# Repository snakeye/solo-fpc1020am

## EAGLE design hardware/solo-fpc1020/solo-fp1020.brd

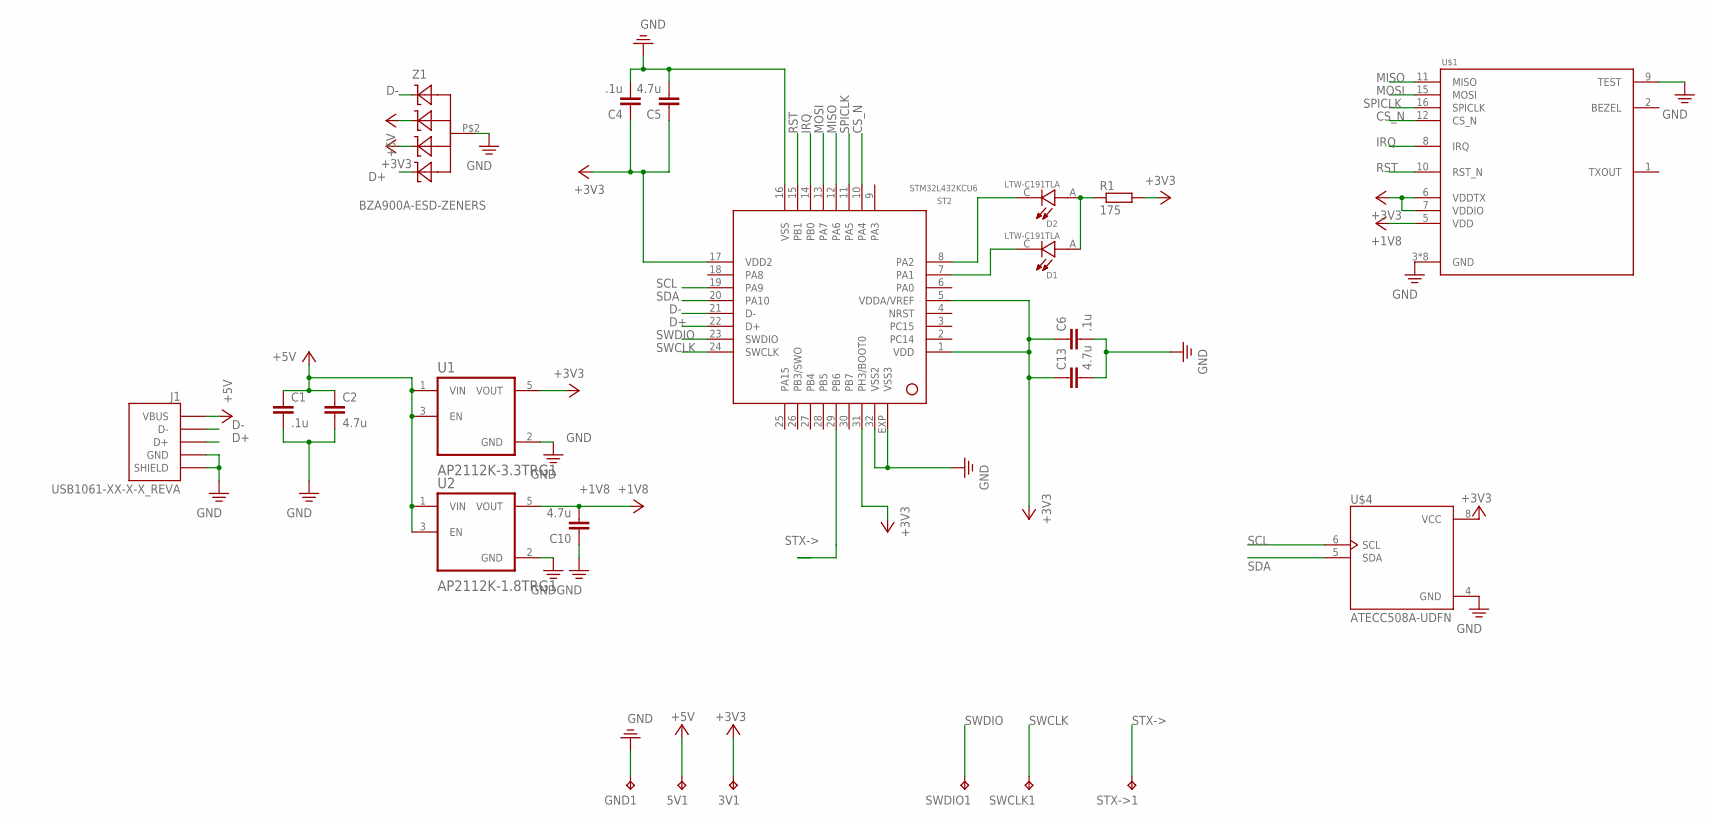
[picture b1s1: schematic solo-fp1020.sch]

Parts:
3V1, 5V1: TEST_POINT; B1,27
C1, C4, C6: .1u; C0603
C2, C5, C10, C13: 4.7u; C0603
D1, D2: LTW-C191TLA; LEDC1608X65N
GND1: TEST_POINT; B1,27
J1: USB1061-XX-X-X_REVA; GCT_USB1061-XX-X-X_REVA
R1: 175; R0603
ST2: STM32L432KCU6; QFN32
STX->1: TEST_POINT; B1,27
SWCLK1: TEST_POINT; B1,27
SWDIO1: TEST_POINT; B1,27
U1: AP2112K-3.3TRG1; SOT95P285X140-5N
U2: AP2112K-1.8TRG1; SOT95P285X140-5N
U$1: FPC1020AM
U$4: ATECC508A-UDFN; SON50P200X300X60-9N
Z1: BZA900A-ESD-ZENERS; BZA900A

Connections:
+1V8: C10.2, U2.5 (VOUT), U$1.5 (VDD)
+3V3: 3V1.TP, C4.1, C5.1, C6.1, C13.1, R1.2, ST2.1 (VDD), ST2.5 (VDDA/VREF), ST2.17 (VDD2), ST2.31 (PH3/BOOT0), U1.5 (VOUT), U$1.6 (VDDTX), U$1.7 (VDDIO), U$4.8 (VCC), Z1.P$5 (C1)
+5V: 5V1.TP, C1.1, C2.1, J1.1 (VBUS), U1.1 (VIN), U1.3 (EN), U2.1 (VIN), U2.3 (EN), Z1.P$1 (C)
CS_N: ST2.10 (PA4), U$1.12 (CS_N)
D+: J1.3 (D+), ST2.22 (D+), Z1.P$3 (C3)
D-: J1.2 (D-), ST2.21 (D-), Z1.P$4 (C2)
GND: C1.2, C2.2, C4.2, C5.2, C6.2, C10.1, C13.2, GND1.TP, J1.4 (GND), J1.5 (SHIELD), J1.6 (SHIELD), ST2.16 (VSS), ST2.32 (VSS2), ST2.EXP (VSS3), U1.2 (GND), U2.2 (GND), U$1.3 (GND), U$1.4 (GND), U$1.9 (TEST), U$1.13 (GND), U$1.14 (GND), U$1.17 (GND), U$1.18 (GND), U$1.19 (GND), U$1.20 (GND), U$4.4 (GND), Z1.P$2
IRQ: ST2.14 (PB0), U$1.8 (IRQ)
MISO: ST2.12 (PA6), U$1.11 (MISO)
MOSI: ST2.13 (PA7), U$1.15 (MOSI)
unnamed: D1.A, D2.A, R1.1
unnamed: D2.C, ST2.8 (PA2)
unnamed: D1.C, ST2.7 (PA1)
RST: ST2.15 (PB1), U$1.10 (RST_N)
SCL: ST2.19 (PA9), U$4.6 (SCL)
SDA: ST2.20 (PA10), U$4.5 (SDA)
SPICLK: ST2.11 (PA5), U$1.16 (SPICLK)
STX->: ST2.29 (PB6), STX->1.TP
SWCLK: ST2.24 (SWCLK), SWCLK1.TP
SWDIO: ST2.23 (SWDIO), SWDIO1.TP

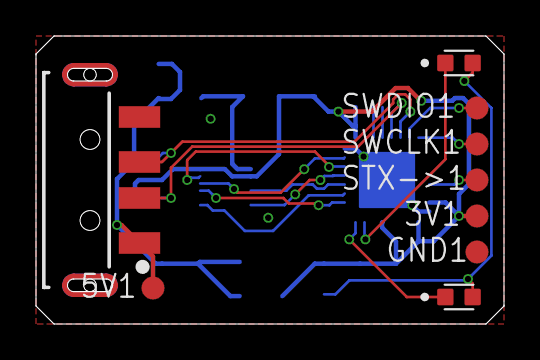
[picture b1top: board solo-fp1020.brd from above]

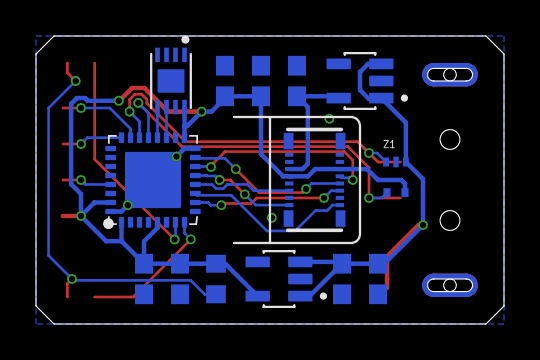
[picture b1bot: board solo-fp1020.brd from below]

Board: 2 copper layers, 26.0 x 16.0 mm, 23 parts (14 on the bottom side), 20 nets.

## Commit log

2023-12-15 Add renovate.json
